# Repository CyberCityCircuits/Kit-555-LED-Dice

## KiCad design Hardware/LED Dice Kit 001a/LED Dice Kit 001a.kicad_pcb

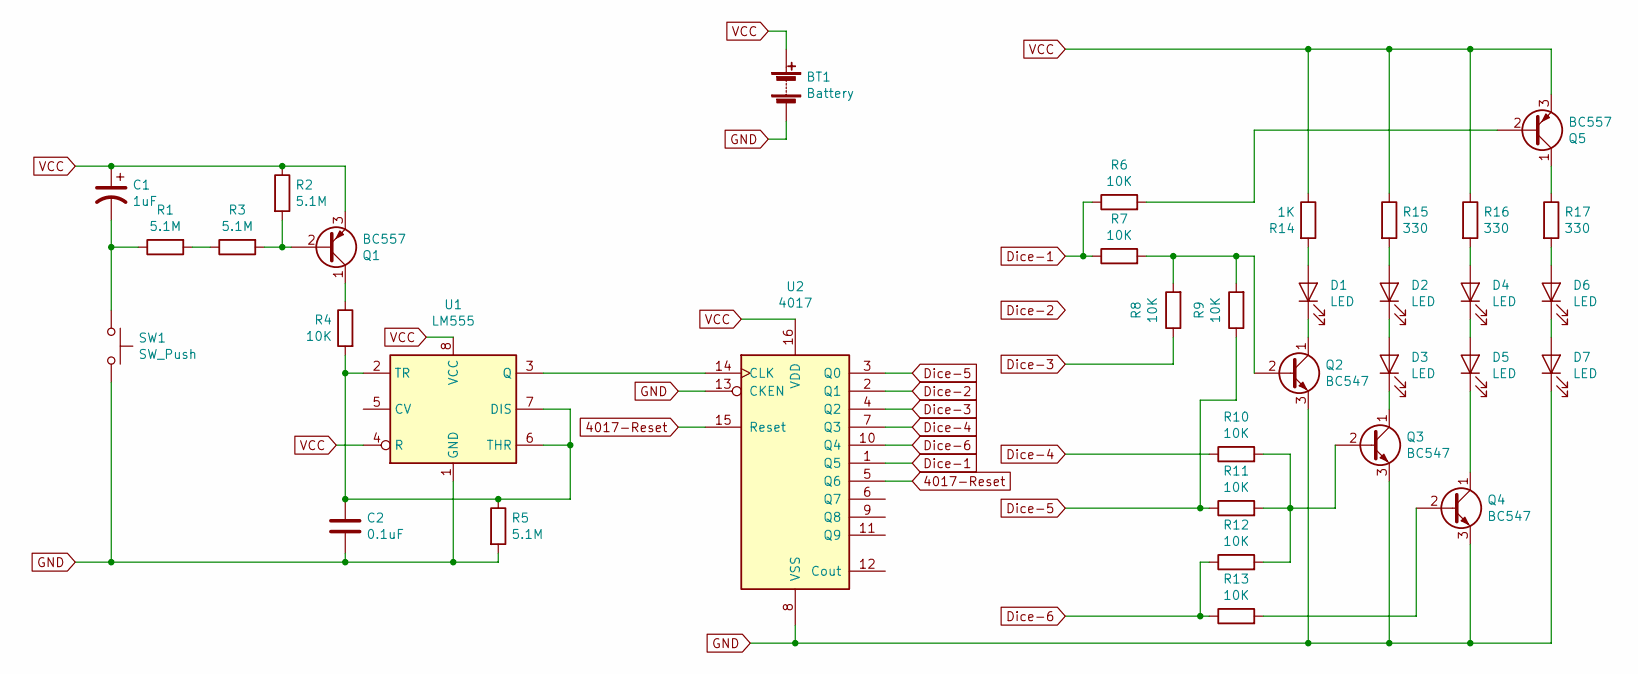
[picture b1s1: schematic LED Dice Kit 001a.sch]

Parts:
BT1: Battery; PinSocket_1x02_P2.54mm_Vertical
C1: 1uF; Schematic - Cap Electrolytic D5 P2
C2: 0.1uF; Schematic - Capacitor 5.0mm
D1, D2, D3, D4, D5, D6, D7: LED; Schematic - LED 5mm(2.56P) 003
Q1, Q5: BC557; TO-92_Inline
Q2, Q3, Q4: BC547; TO-92_Inline
R1, R2, R3, R5: 5.1M; Schematic - Resistor 7.62mm
R4, R6, R7, R8, R9, R10, R11, R12, R13: 10K; Schematic - Resistor 7.62mm
R14: 1K; Schematic - Resistor 7.62mm
R15, R16, R17: 330; Schematic - Resistor 7.62mm
SW1: SW_Push; Schematic - Push Button 6.5x4.5
U1: LM555; DIP-8_W7.62mm_LongPads
U2: 4017; DIP-16_W7.62mm_LongPads

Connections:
4017-Reset: U2.5 (Q6), U2.15 (Reset)
Dice-1: R6.1, R7.1, U2.1 (Q5)
Dice-2: U2.2 (Q1)
Dice-3: R8.1, U2.4 (Q2)
Dice-4: R10.1, U2.7 (Q3)
Dice-5: R9.1, R11.1, U2.3 (Q0)
Dice-6: R12.1, R13.1, U2.10 (Q4)
GND: BT1.2 (-), C2.2, D7.1 (K), Q2.3 (E), Q3.3 (E), Q4.3 (E), R5.2, SW1.2, U1.1 (GND), U2.8 (VSS), U2.13 (CKEN)
unnamed: C1.2, R1.1, SW1.1
unnamed: C2.1, R4.2, R5.1, U1.2 (TR), U1.6 (THR), U1.7 (DIS)
unnamed: D1.1 (K), Q2.1 (C)
unnamed: D1.2 (A), R14.2
unnamed: D2.1 (K), D3.2 (A)
unnamed: D2.2 (A), R15.2
unnamed: D3.1 (K), Q3.1 (C)
unnamed: D4.1 (K), D5.2 (A)
unnamed: D4.2 (A), R16.2
unnamed: D5.1 (K), Q4.1 (C)
unnamed: D6.1 (K), D7.2 (A)
unnamed: D6.2 (A), R17.2
unnamed: Q1.1 (C), R4.1
unnamed: Q1.2 (B), R2.2, R3.2
unnamed: Q2.2 (B), R7.2, R8.2, R9.2
unnamed: Q3.2 (B), R10.2, R11.2, R12.2
unnamed: Q4.2 (B), R13.2
unnamed: Q5.1 (C), R17.1
unnamed: Q5.2 (B), R6.2
unnamed: R1.2, R3.1
unnamed: U1.3 (Q), U2.14 (CLK)
VCC: BT1.1 (+), C1.1, Q1.3 (E), Q5.3 (E), R2.1, R14.1, R15.1, R16.1, U1.4 (R), U1.8 (VCC), U2.16 (VDD)

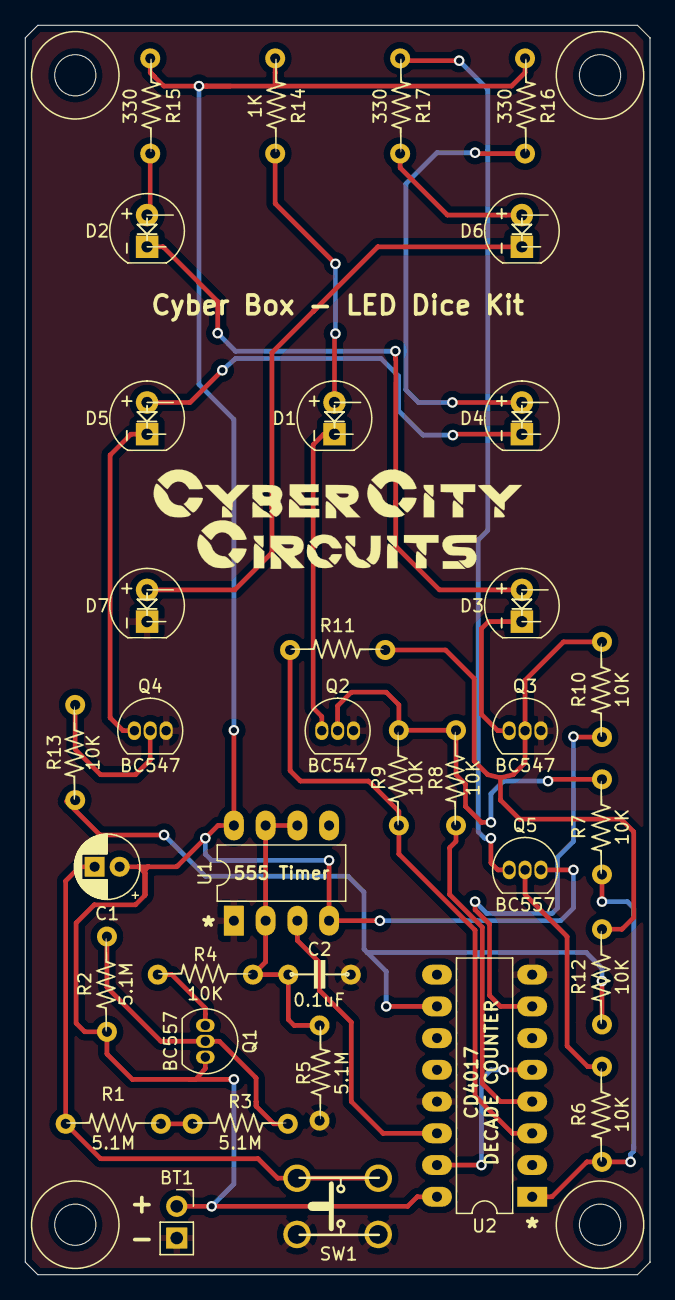
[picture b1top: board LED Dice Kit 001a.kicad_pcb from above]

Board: 2 copper layers, 50.0 x 100.0 mm, 39 parts (0 on the bottom side), 29 nets.

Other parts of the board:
 : 3mm_Hole; 3mm Mount Hole
 #2,  #3,  #4: 3mm_Hole; 3mm Mount Hole
